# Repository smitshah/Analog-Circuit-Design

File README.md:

# Analog-Circuit-Design
Examples of Analog Circuit in KiCAD and LTspice

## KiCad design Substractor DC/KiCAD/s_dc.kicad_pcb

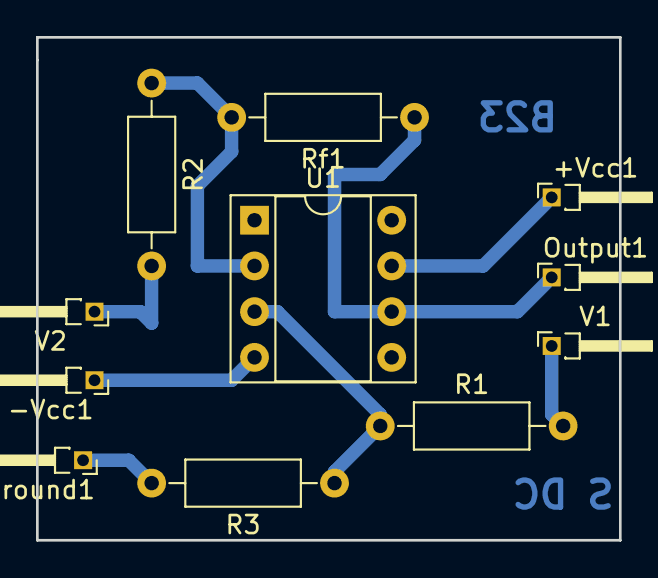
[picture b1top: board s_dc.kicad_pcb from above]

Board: 2 copper layers, 32.4 x 27.9 mm, 11 parts (0 on the bottom side), 8 nets.

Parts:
+Vcc1: +12V; Pin_Header_Angled_1x01_Pitch1.27mm
-Vcc1: -12V; Pin_Header_Angled_1x01_Pitch1.27mm
Ground1: Gnd; Pin_Header_Angled_1x01_Pitch1.27mm
Output1: CRO; Pin_Header_Angled_1x01_Pitch1.27mm
R1, R2, R3: 1k ohm; R_Axial_DIN0207_L6.3mm_D2.5mm_P10.16mm_Horizontal
Rf1: 1k ohm; R_Axial_DIN0207_L6.3mm_D2.5mm_P10.16mm_Horizontal
U1: LM741; DIP-8_W7.62mm_Socket
V1: 1V; Pin_Header_Angled_1x01_Pitch1.27mm
V2: 5V; Pin_Header_Angled_1x01_Pitch1.27mm

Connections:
unnamed: +Vcc1.1, U1.7
unnamed: -Vcc1.1, U1.4
unnamed: Ground1.1, R3.2
unnamed: Output1.1, Rf1.1, U1.6
unnamed: R1.1, R3.1, U1.3
unnamed: R1.2, V1.1
unnamed: R2.1, Rf1.2, U1.2
unnamed: R2.2, V2.1

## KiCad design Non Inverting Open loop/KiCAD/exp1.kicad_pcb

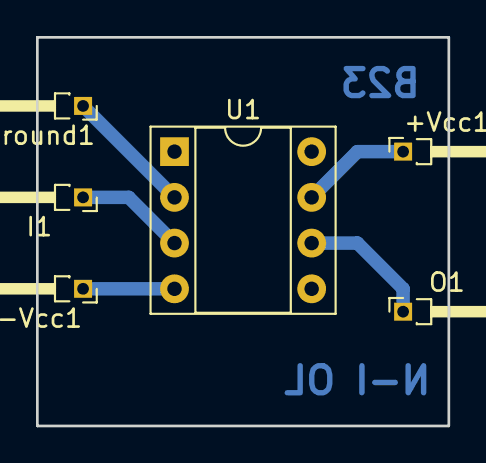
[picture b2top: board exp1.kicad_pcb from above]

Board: 2 copper layers, 22.9 x 21.6 mm, 6 parts (0 on the bottom side), 5 nets.

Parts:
+Vcc1: +12V; Pin_Header_Angled_1x01_Pitch1.27mm
-Vcc1: -12V; Pin_Header_Angled_1x01_Pitch1.27mm
Ground1: Gnd; Pin_Header_Angled_1x01_Pitch1.27mm
I1: sine 2 1kHz; Pin_Header_Angled_1x01_Pitch1.27mm
O1: CRO; Pin_Header_Angled_1x01_Pitch1.27mm
U1: LM741; DIP-8_W7.62mm_Socket

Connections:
unnamed: +Vcc1.1, U1.7
unnamed: -Vcc1.1, U1.4
unnamed: Ground1.1, U1.2
unnamed: I1.1, U1.3
unnamed: O1.1, U1.6

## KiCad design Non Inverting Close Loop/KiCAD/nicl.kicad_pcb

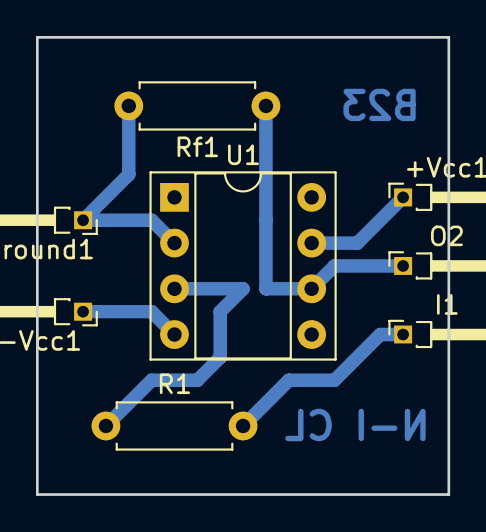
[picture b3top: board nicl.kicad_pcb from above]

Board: 2 copper layers, 22.9 x 25.4 mm, 8 parts (0 on the bottom side), 6 nets.

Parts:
+Vcc1: +12V; Pin_Header_Angled_1x01_Pitch1.27mm
-Vcc1: -12V; Pin_Header_Angled_1x01_Pitch1.27mm
Ground1: Gnd; Pin_Header_Angled_1x01_Pitch1.27mm
I1: sine 2V 1kHz; Pin_Header_Angled_1x01_Pitch1.27mm
O2: CRO; Pin_Header_Angled_1x01_Pitch1.27mm
R1: 1k ohm; R_Axial_DIN0207_L6.3mm_D2.5mm_P7.62mm_Horizontal
Rf1: 5k ohm; R_Axial_DIN0207_L6.3mm_D2.5mm_P7.62mm_Horizontal
U1: LM741; DIP-8_W7.62mm_Socket

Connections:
unnamed: +Vcc1.1, U1.7
unnamed: -Vcc1.1, U1.4
unnamed: Ground1.1, Rf1.2, U1.2
unnamed: I1.1, R1.2
unnamed: O2.1, Rf1.1, U1.6
unnamed: R1.1, U1.3

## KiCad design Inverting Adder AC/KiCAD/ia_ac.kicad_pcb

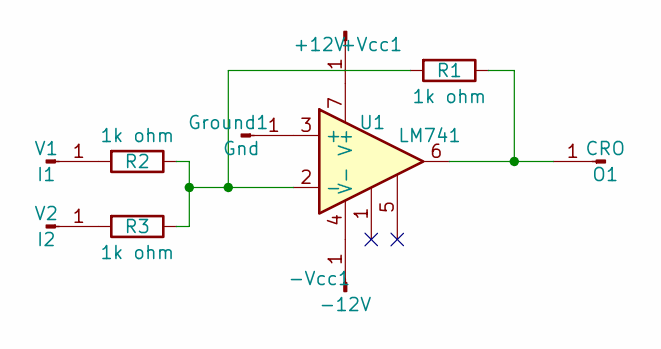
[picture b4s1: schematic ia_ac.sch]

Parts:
+Vcc1: +12V; Pin_Header_Angled_1x01_Pitch1.27mm
-Vcc1: -12V; Pin_Header_Angled_1x01_Pitch1.27mm
Ground1: Gnd; Pin_Header_Angled_1x01_Pitch1.27mm
O1: CRO; Pin_Header_Angled_1x01_Pitch1.27mm
R1, R2, R3: 1k ohm; R_Axial_DIN0207_L6.3mm_D2.5mm_P7.62mm_Horizontal
U1: LM741; DIP-8_W7.62mm_Socket
V1: I1; Pin_Header_Angled_1x01_Pitch1.27mm
V2: I2; Pin_Header_Angled_1x01_Pitch1.27mm

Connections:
unnamed: +Vcc1.1, U1.7 (V+)
unnamed: -Vcc1.1, U1.4 (V-)
unnamed: Ground1.1, U1.3 (+)
unnamed: O1.1, R1.1, U1.6
unnamed: R1.2, R2.1, R3.1, U1.2 (-)
unnamed: R2.2, V1.1
unnamed: R3.2, V2.1

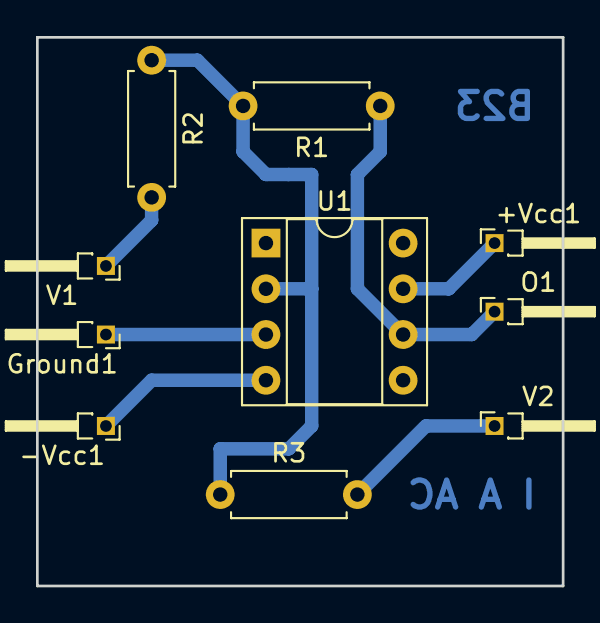
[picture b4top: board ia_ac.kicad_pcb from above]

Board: 2 copper layers, 29.2 x 30.5 mm, 10 parts (0 on the bottom side), 7 nets.
